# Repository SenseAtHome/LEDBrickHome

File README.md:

# LEDBrickHome

Wi-Fi controller compatible with various Lego Lighting kits, designed to enable integration of lighting into Home Assistant via ESPHome.  Supports single colour and RGB dimmable lights, lighting effects and use in scenes.

## Versions

> [!WARNING]  
> Versions up to and included v1.1 have a hardware design issue that prevents the use of USB-C to USB-C cables.  They will work correctly with USB-A to USB-C cables.

Different versions of LEDBrickHome may exist in the future with different numbers of output connectors (e.g. to reduce cost or size).

To maximise available number of channels, RGB (4-pin) outputs are shared with single colour (2-pin) outputs.  In other words, a 16 PWM controller can support a total of 16 different outputs of a single colour, but for each RGB output used, three single colour outputs are lost.

| Version | Total PWM Outputs | 2-pin outputs | 4-pin outputs | Dimensions |
| --- | --- | --- | --- | --- |
| 16ch-v1.0 | 16 | 16 | 5 | 96 x 45 mm |
| 16ch-v1.1 | 16 | 16 | 5 | 68 x 45 mm |

### 16ch-v1

16ch-v1 is based on an ESP32-WROOM (exact memory size does not matter), uses a CP2102N ([drivers](https://www.silabs.com/developers/usb-to-uart-bridge-vcp-drivers?tab=downloads)) for it's USB->UART bridge, and is powered by a USB-C connector.  Outputs are grouped in blocks and identified on the silkscreen which 2-pin outputs are shared with 4-pin outputs.

### 16ch-v1.1

16ch-v1.1 is a smaller version of the previous 16ch design, using a CH340C ([drivers](http://www.wch-ic.com/downloads/CH341SER_ZIP.html)) for it's USB->UART bridge, but is otherwise functionally identical.

## Effects
Various effects are available in ESPHome, which are explained in the [documentation](https://esphome.io/components/light/index.html#light-effects), some of these are included in the code examples already.  For flickering torch effects, the default flicker intensity (of 1.5%) will want to be increased.  The demo video above has flicker set at 10%.

## Compatibility

LEDBrickHome is compatible with lighting kits that use a JST SUR connector with 5V on pin 1, and switched 0V on pin 2 (plus pins 3 & 4 for RGB connectors).

The below table shows the results of our testing.  You should verify connector type and pinout yourself for your own project.

| Light System | Compatible? | Notes |
| --- | --- | --- |
| Light My Bricks V1 | :white_check_mark: | | 
| Light My Bricks V2 | :x: | Swapped to a flat ribbon style connector |
| Briksmax V1 | :white_check_mark: | |
| Briksmax V2 | :x: | Similar but not compatible with JST SUR |
| Kyglaring | :white_check_mark: | |

Note, order of Red, Green and Blue channels is not important and can be changed in your configuration file.

## PCB Design

The PCB design is created in KiCAD V7, and is a simple 2-layer PCB.

## Tips
* Do not add the web server to the code, this seems to cause the ESP32 to reboot regularly.
* Boot and Reset buttons are included, but shouldn't be required for programming
* Original ESP32's are used rather than newer parts (e.g. S3, C3, etc.) as the original parts support 16 PWM outputs, whereas the newer parts only support 8 PWM outputs.
* RGB outputs may need their output channels swapping if the colour mapping is wrong. i.e. if you ask for Red but get Green, change the appropriate lines in your configuration file.

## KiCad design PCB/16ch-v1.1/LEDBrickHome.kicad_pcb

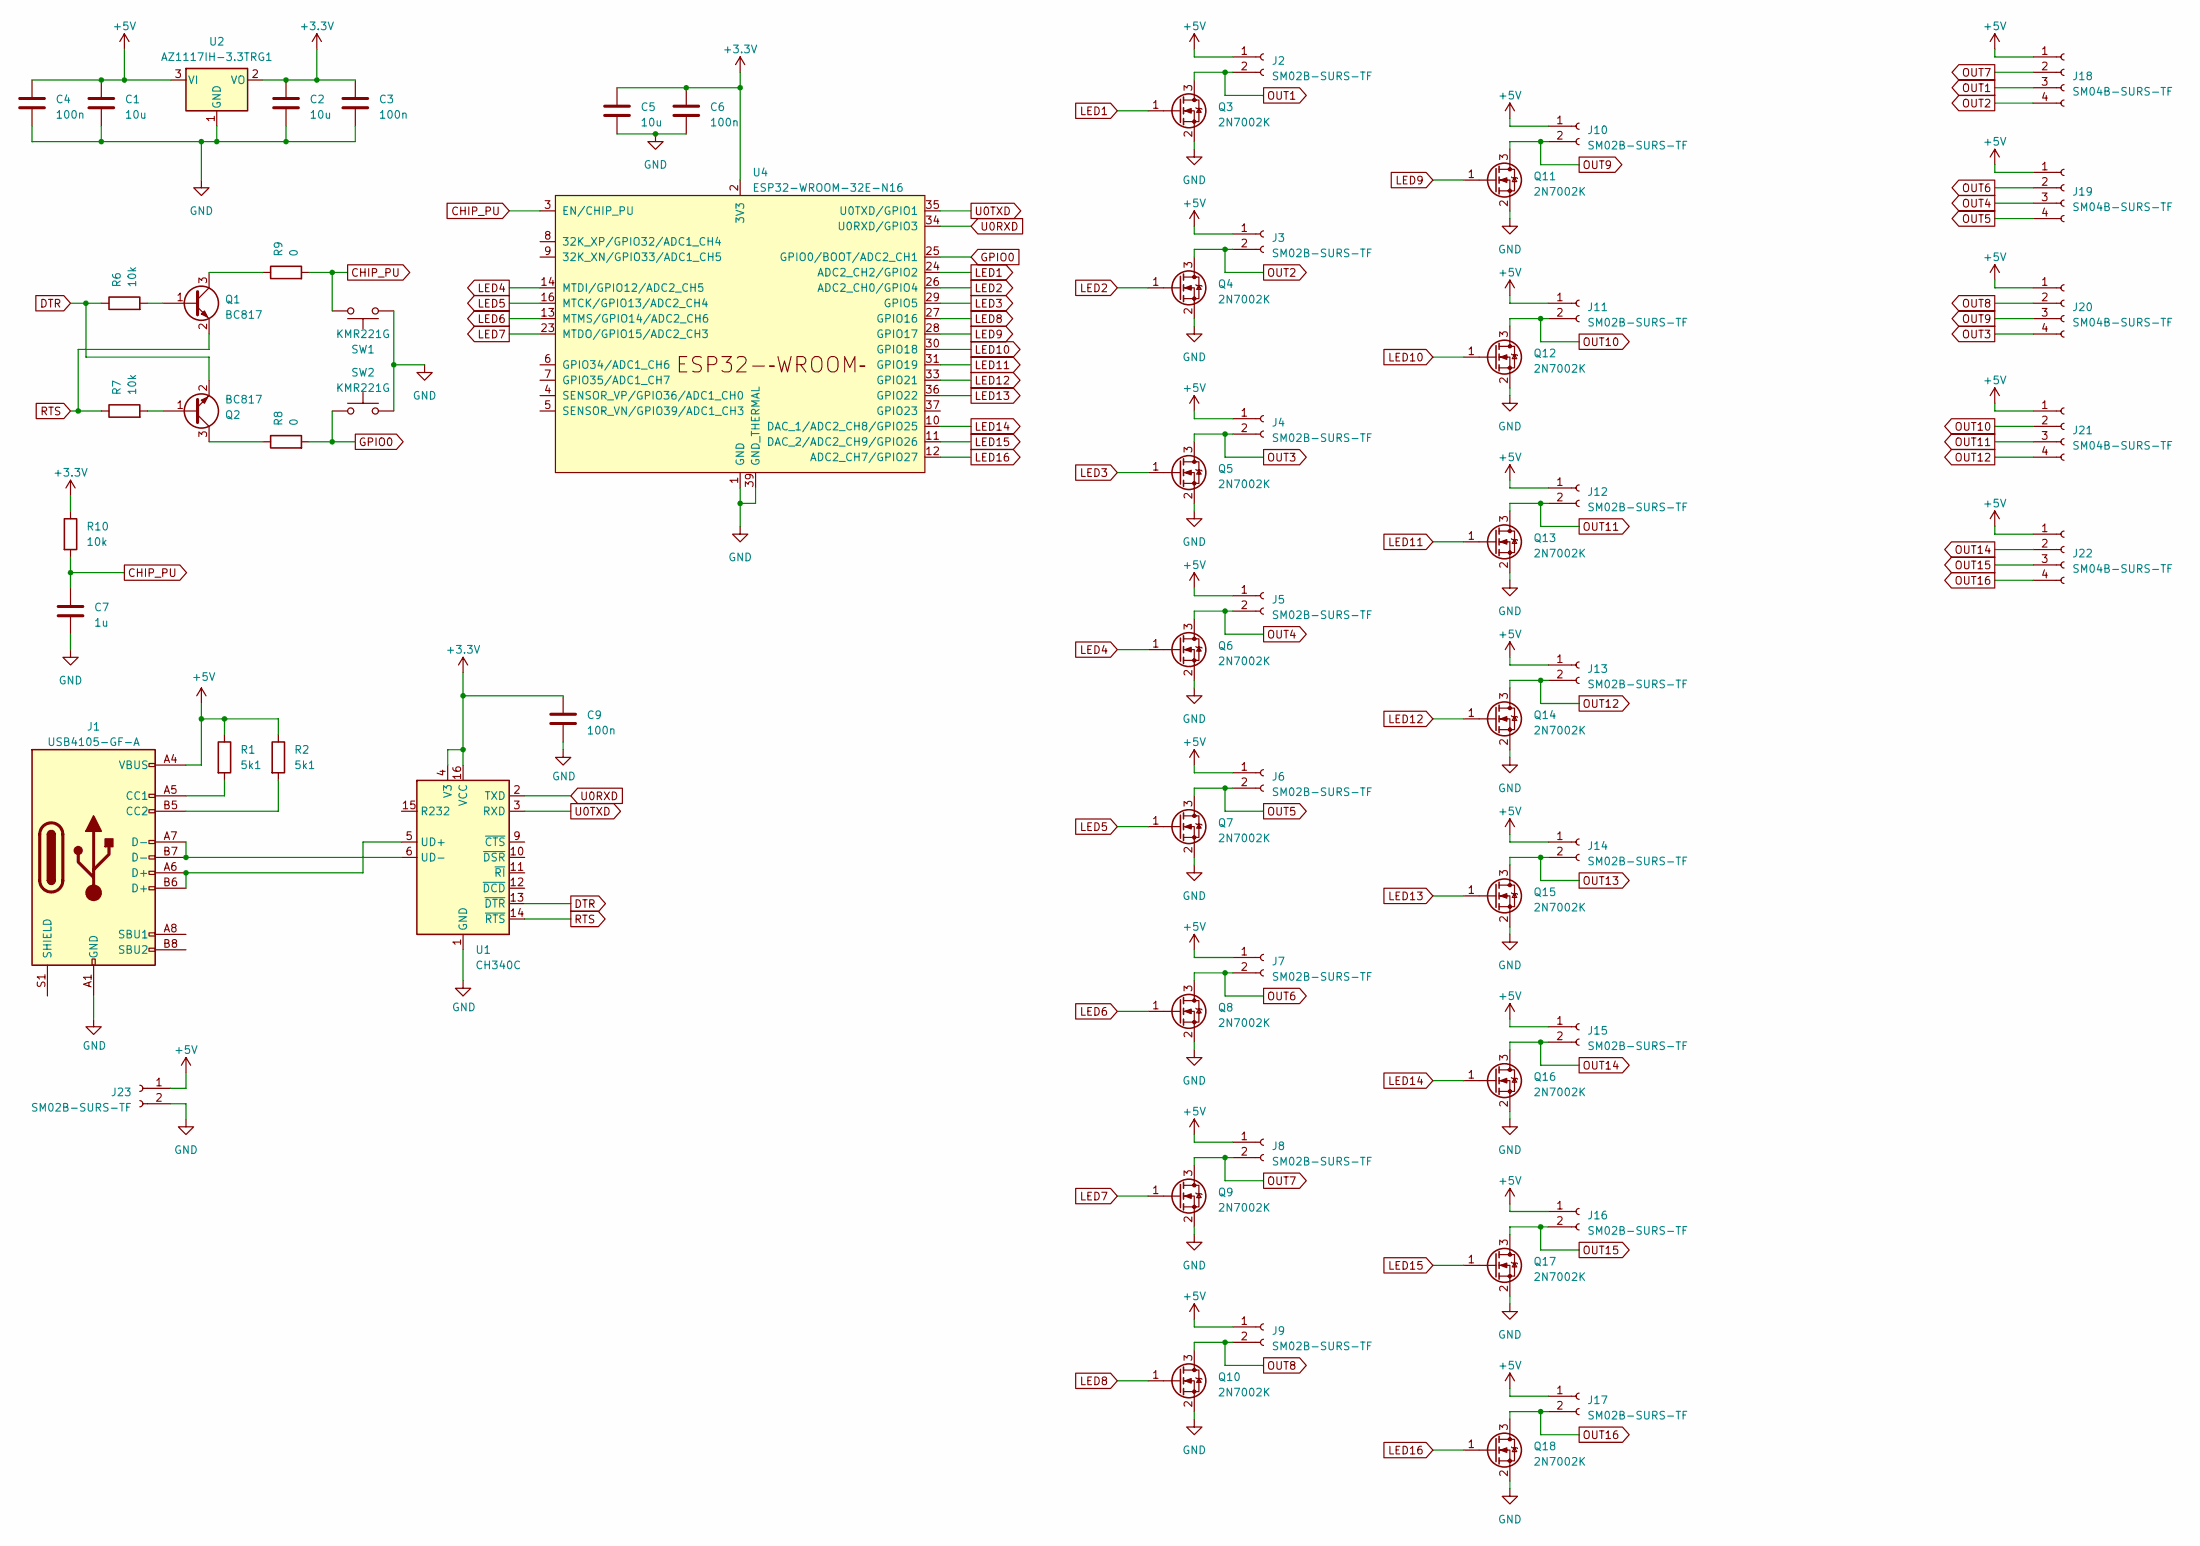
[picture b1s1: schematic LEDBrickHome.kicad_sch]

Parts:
C1, C2, C5: 10u; C_0603_1608Metric
C3, C4, C6, C9: 100n; C_0603_1608Metric
C7: 1u; C_0603_1608Metric
J1: USB4105-GF-A; USB_C_Receptacle_GCT_USB4105-xx-A_16P_TopMnt_Horizontal
J2, J3, J4, J5, J6, J7, J8, J9, J10, J11, J12, J13, J14, J15, J16, J17, J23: SM02B-SURS-TF; JST_SUR_SM02B-SURS-TF_1x02-1MP_P0.80mm_Horizontal
J18, J19, J20, J21, J22: SM04B-SURS-TF; JST_SUR_SM04B-SURS-TF_1x04-1MP_P0.80mm_Horizontal
Q1, Q2: BC817; SOT-23
Q3, Q4, Q5, Q6, Q7, Q8, Q9, Q10, Q11, Q12, Q13, Q14, Q15, Q16, Q17, Q18: 2N7002K; SOT-23
R1, R2: 5k1; R_0402_1005Metric
R6, R7, R10: 10k; R_0402_1005Metric
R8, R9: 0; R_0402_1005Metric
SW1, SW2: KMR221G; SW_Push_1P1T_NO_CK_KMR2
U1: CH340C; SOIC-16_3.9x9.9mm_P1.27mm
U2: AZ1117IH-3.3TRG1; SOT-223-3_TabPin2
U4: ESP32-WROOM-32E-N16; ESP32-WROOM-32E

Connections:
+3.3V: C2.2, C3.2, C5.2, C6.2, C9.2, R10.1, U1.4 (V3), U1.16 (VCC), U2.2 (VO), U4.2 (3V3)
+5V: C1.2, C4.2, J1.A4 (VBUS), J1.A9 (VBUS), J1.B4 (VBUS), J1.B9 (VBUS), J2.1, J2.MP, J3.1, J3.MP, J4.1, J4.MP, J5.1, J5.MP, J6.1, J6.MP, J7.1, J7.MP, J8.1, J8.MP, J9.1, J9.MP, J10.1, J10.MP, J11.1, J11.MP, J12.1, J12.MP, J13.1, J13.MP, J14.1, J14.MP, J15.1, J15.MP, J16.1, J16.MP, J17.1, J17.MP, J18.1, J18.MP, J19.1, J19.MP, J20.1, J20.MP, J21.1, J21.MP, J22.1, J22.MP, J23.1, J23.MP, R1.1, R2.1, U2.3 (VI)
CHIP_PU: C7.2, R9.2, R10.2, SW1.1, U4.3 (EN/CHIP_PU)
DTR: Q2.2 (E), R6.1, U1.13 (~DTR)
GND: C1.1, C2.1, C3.1, C4.1, C5.1, C6.1, C7.1, C9.1, J1.A1 (GND), J1.A12 (GND), J1.B1 (GND), J1.B12 (GND), J23.2, Q3.2 (S), Q4.2 (S), Q5.2 (S), Q6.2 (S), Q7.2 (S), Q8.2 (S), Q9.2 (S), Q10.2 (S), Q11.2 (S), Q12.2 (S), Q13.2 (S), Q14.2 (S), Q15.2 (S), Q16.2 (S), Q17.2 (S), Q18.2 (S), SW1.2, SW2.2, U1.1 (GND), U2.1 (GND), U4.1 (GND), U4.15 (GND), U4.38 (GND), U4.39 (GND_THERMAL)
GPIO0: R8.2, SW2.1, U4.25 (GPIO0/BOOT/ADC2_CH1)
LED1: Q3.1 (G), U4.24 (ADC2_CH2/GPIO2)
LED2: Q4.1 (G), U4.26 (ADC2_CH0/GPIO4)
LED3: Q5.1 (G), U4.29 (GPIO5)
LED4: Q6.1 (G), U4.14 (MTDI/GPIO12/ADC2_CH5)
LED5: Q7.1 (G), U4.16 (MTCK/GPIO13/ADC2_CH4)
LED6: Q8.1 (G), U4.13 (MTMS/GPIO14/ADC2_CH6)
LED7: Q9.1 (G), U4.23 (MTDO/GPIO15/ADC2_CH3)
LED8: Q10.1 (G), U4.27 (GPIO16)
LED9: Q11.1 (G), U4.28 (GPIO17)
LED10: Q12.1 (G), U4.30 (GPIO18)
LED11: Q13.1 (G), U4.31 (GPIO19)
LED12: Q14.1 (G), U4.33 (GPIO21)
LED13: Q15.1 (G), U4.36 (GPIO22)
LED14: Q16.1 (G), U4.10 (DAC_1/ADC2_CH8/GPIO25)
LED15: Q17.1 (G), U4.11 (DAC_2/ADC2_CH9/GPIO26)
LED16: Q18.1 (G), U4.12 (ADC2_CH7/GPIO27)
unnamed: J1.A5 (CC1), R1.2
unnamed: J1.B5 (CC2), R2.2
unnamed: Q1.1 (B), R6.2
unnamed: Q1.3 (C), R9.1
unnamed: Q2.1 (B), R7.2
unnamed: Q2.3 (C), R8.1
unnamed: J1.A6 (D+), J1.B6 (D+), U1.5 (UD+)
unnamed: J1.A7 (D-), J1.B7 (D-), U1.6 (UD-)
OUT1: J2.2, J18.3, Q3.3 (D)
OUT2: J3.2, J18.4, Q4.3 (D)
OUT3: J4.2, J20.4, Q5.3 (D)
OUT4: J5.2, J19.3, Q6.3 (D)
OUT5: J6.2, J19.4, Q7.3 (D)
OUT6: J7.2, J19.2, Q8.3 (D)
OUT7: J8.2, J18.2, Q9.3 (D)
OUT8: J9.2, J20.2, Q10.3 (D)
OUT9: J10.2, J20.3, Q11.3 (D)
OUT10: J11.2, J21.2, Q12.3 (D)
OUT11: J12.2, J21.3, Q13.3 (D)
OUT12: J13.2, J21.4, Q14.3 (D)
OUT13: J14.2, Q15.3 (D)
OUT14: J15.2, J22.2, Q16.3 (D)
OUT15: J16.2, J22.3, Q17.3 (D)
OUT16: J17.2, J22.4, Q18.3 (D)
RTS: Q1.2 (E), R7.1, U1.14 (~RTS)
U0RXD: U1.2 (TXD), U4.34 (U0RXD/GPIO3)
U0TXD: U1.3 (RXD), U4.35 (U0TXD/GPIO1)

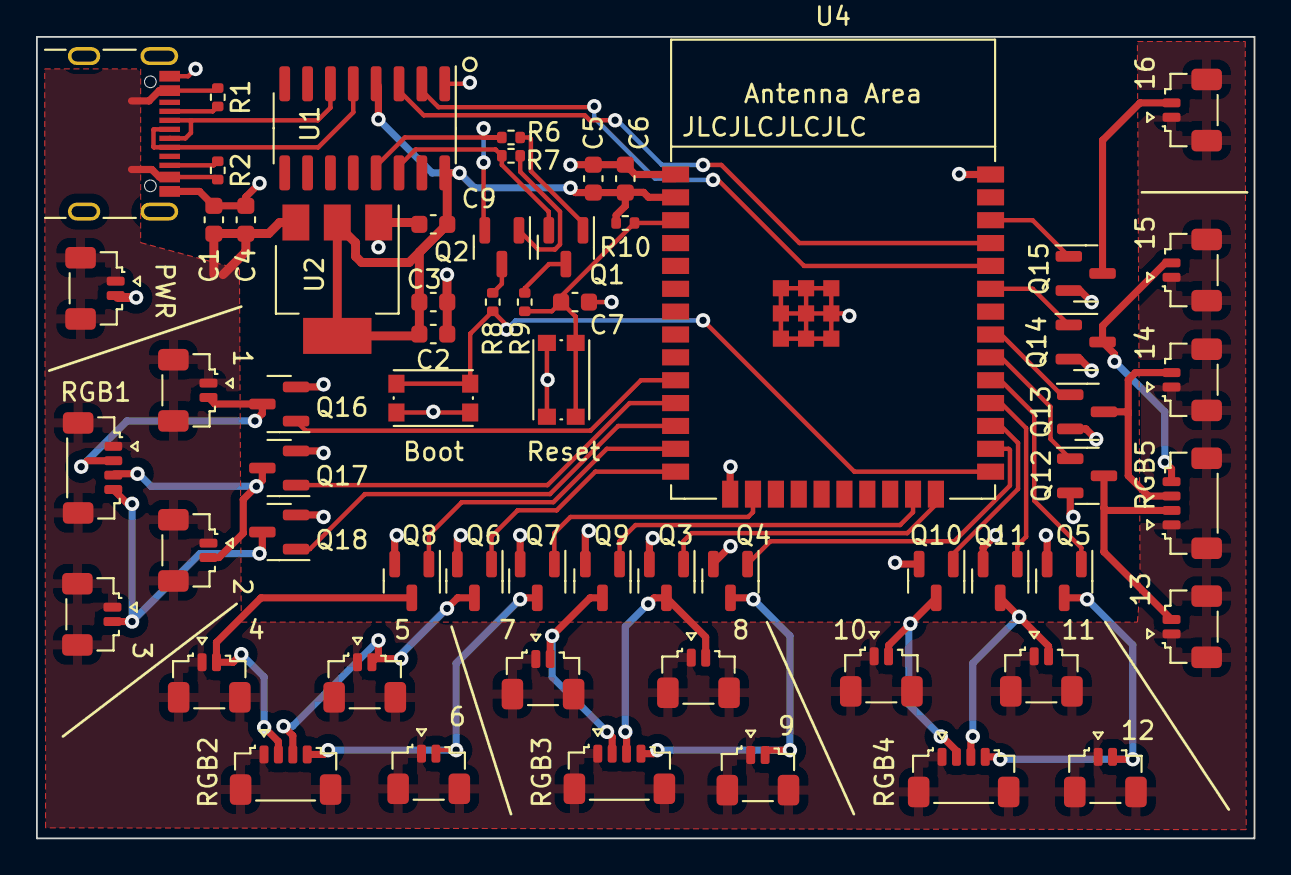
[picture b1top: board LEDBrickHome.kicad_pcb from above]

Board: 2 copper layers, 67.6 x 44.5 mm, 61 parts (0 on the bottom side), 49 nets.

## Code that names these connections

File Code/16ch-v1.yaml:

substitutions:
  name: "ledbrickhome-16ch"
  friendly_name: "LEDBrickHome"
  project_name: "SenseAtHome.ledbrickhome-16ch"
  project_version: "1.0"
  hidden_ssid: "false"

esphome:
  name: "${name}"
  name_add_mac_suffix: true
  project:
    name: "${project_name}"
    version: "${project_version}"

esp32:
  board: esp32dev
  framework:
    type: arduino
    version: recommended

logger:

api:

ota:
  - platform: esphome

wifi:
  fast_connect: ${hidden_ssid}
  ap: {}

captive_portal:

improv_serial:

esp32_improv:
  authorizer: none
  
dashboard_import:
  package_import_url: github://AlexCPU/LEDBrickHome/Code/16ch-v1.yaml@main
  import_full_config: true

binary_sensor:
  - platform: status
    name: "${friendly_name} Status"

sensor:
  - platform: uptime
    name: "${friendly_name} Uptime"
    disabled_by_default: true

button:
  - platform: restart
    id: restart_button
    name: "${friendly_name} Restart"
  - platform: factory_reset
    name: Restart with Factory Default Settings

time:
  - platform: sntp

switch:
  - platform: factory_reset
    name: Factory Reset

text_sensor:
  - platform: wifi_info
    ip_address:
      name: "${friendly_name} IP Address"
      disabled_by_default: true

light:
# Details for each of the outputs.
# see https://esphome.io/components/light/index.html#light-effects for configuration
# of light effects

# Group 1:
# to use RGB light, uncomment it's section and comment the monochromatic lights
  - platform: monochromatic
    name: "Channel 1"
    output: output_ch1
    effects:
      - pulse:
      - flicker:
          intensity: 10%
      - strobe:
  - platform: monochromatic
    name: "Channel 2"
    output: output_ch2
    effects:
      - pulse:
      - flicker:
          intensity: 10%
      - strobe:
  - platform: monochromatic
    name: "Channel 3"
    output: output_ch3
    effects:
      - pulse:
      - flicker:
          intensity: 10%
      - strobe:
#  - platform: rgb
#    name: "RGB1"
#    # Output channels may need swapping to match the wiring of your light
#    red: output_ch1
#    green: output_ch2
#    blue: output_ch3
#    effects:
#      - pulse:
#      - flicker:
#      - strobe:
#      - random:

# Group 2:
# to use RGB light, uncomment it's section and comment the monochromatic lights
  - platform: monochromatic
    name: "Channel 4"
    output: output_ch4
    effects:
      - pulse:
      - flicker:
          intensity: 10%
      - strobe:
  - platform: monochromatic
    name: "Channel 5"
    output: output_ch5
    effects:
      - pulse:
      - flicker:
          intensity: 10%
      - strobe:
  - platform: monochromatic
    name: "Channel 6"
    output: output_ch6
    effects:
      - pulse:
      - flicker:
          intensity: 10%
      - strobe:
#  - platform: rgb
#    name: "RGB2"
#    # Output channels may need swapping to match the wiring of your light
#    red: output_ch4
#    green: output_ch5
#    blue: output_ch6
#    effects:
#      - pulse:
#      - flicker:
#      - strobe:
#      - random:

# Group 3:
# to use RGB light, uncomment it's section and comment the monochromatic lights
  - platform: monochromatic
    name: "Channel 7"
    output: output_ch7
    effects:
      - pulse:
      - flicker:
          intensity: 10%
      - strobe:
  - platform: monochromatic
    name: "Channel 8"
    output: output_ch8
    effects:
      - pulse:
      - flicker:
          intensity: 10%
      - strobe:
  - platform: monochromatic
    name: "Channel 9"
    output: output_ch9
    effects:
      - pulse:
      - flicker:
          intensity: 10%
      - strobe:
#  - platform: rgb
#    name: "RGB3"
#    # Output channels may need swapping to match the wiring of your light
#    red: output_ch7
#    green: output_ch8
#    blue: output_ch9
#    effects:
#      - pulse:
#      - flicker:
#      - strobe:
#      - random:

# Group 4:
# to use RGB light, uncomment it's section and comment the monochromatic lights
  - platform: monochromatic
    name: "Channel 10"
    output: output_ch10
    effects:
      - pulse:
      - flicker:
          intensity: 10%
      - strobe:
  - platform: monochromatic
    name: "Channel 11"
    output: output_ch11
    effects:
      - pulse:
      - flicker:
          intensity: 10%
      - strobe:
  - platform: monochromatic
    name: "Channel 12"
    output: output_ch12
    effects:
      - pulse:
      - flicker:
          intensity: 10%
      - strobe:
#  - platform: rgb
#    name: "RGB4"
#    # Output channels may need swapping to match the wiring of your light
#    red: output_ch10
#    green: output_ch11
#    blue: output_ch12
#    effects:
#      - pulse:
#      - flicker:
#      - strobe:
#      - random:

# Group 5:
# to use RGB light, uncomment it's section and comment the monochromatic lights
  - platform: monochromatic
    name: "Channel 13"
    output: output_ch13
    effects:
      - pulse:
      - flicker:
          intensity: 10%
      - strobe:
  - platform: monochromatic
    name: "Channel 14"
    output: output_ch14
    effects:
      - pulse:
      - flicker:
          intensity: 10%
      - strobe:
  - platform: monochromatic
    name: "Channel 15"
    output: output_ch15
    effects:
      - pulse:
      - flicker:
          intensity: 10%
      - strobe:
#  - platform: rgb
#    name: "RGB5"
#    # Output channels may need swapping to match the wiring of your light
#    red: output_ch13
#    green: output_ch14
#    blue: output_ch15
#    effects:
#      - pulse:
#      - flicker:
#      - strobe:
#      - random:

# Ungrouped light (always available)
  - platform: monochromatic
    name: "Channel 16"
    output: output_ch16
    effects:
      - pulse:
      - flicker:
          intensity: 10%
      - strobe:

# The output definitions should not need to be changed
output:
  - platform: ledc
    pin: GPIO25
    id: output_ch1
  - platform: ledc
    pin: GPIO26
    id: output_ch2
  - platform: ledc
    pin: GPIO27
    id: output_ch3
  - platform: ledc
    pin: GPIO14
    id: output_ch4
  - platform: ledc
    pin: GPIO12
    id: output_ch5
  - platform: ledc
    pin: GPIO13
    id: output_ch6
  - platform: ledc
    pin: GPIO15
    id: output_ch7
  - platform: ledc
    pin: GPIO2
    id: output_ch8
  - platform: ledc
    pin: GPIO4
    id: output_ch9
  - platform: ledc
    pin: GPIO16
    id: output_ch10
  - platform: ledc
    pin: GPIO17
    id: output_ch11
  - platform: ledc
    pin: GPIO5
    id: output_ch12
  - platform: ledc
    pin: GPIO18
    id: output_ch13
  - platform: ledc
    pin: GPIO19
    id: output_ch14
  - platform: ledc
    pin: GPIO21
    id: output_ch15
  - platform: ledc
    pin: GPIO22
    id: output_ch16

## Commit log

2023-05-10 Create LICENSE
2023-05-29 Add 16ch-v1 prototype
2023-05-29 prototype 16ch yaml code
2023-06-01 Add images
2023-06-06 Add dimensions
2023-06-07 Add 16ch-v1.1
2023-06-24 remove web_server
2023-06-25 Add missing Silkscreen + fix spelling mistake
2023-07-03 Updated compatibility
2023-09-10 Add factory reset
2023-11-22 Add factory reset button
2023-11-29 Update URL
2025-01-08 Update compatability
2025-05-08 Add warning about USB-C cables
